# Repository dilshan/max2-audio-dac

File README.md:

# 24-bit Stereo Audio DAC for Raspberry Pi

This is a 24-bit stereo DAC, which is specifically built for Raspberry Pi boards. This R-2R ladder DAC is developing around Intel / Altera *EPM240T100C5N* CPLD.

DAC which described in this repo can directly connect with the I2S interface of Raspberry Pi boards. The recommended supply voltage for this DAC is 5V to 8V.

The *MCP602* opamp of this module is capable to drive headphone directly. An external AF power amplifier must pair with this module to obtain a higher output power.

This repository contains all the files and binaries to build DAC, which including *Intel Quartus* Project files, Raspberry Pi Device Tree Overlays, etc.

This is certified open-source hardware project. All the content of this project are distributed under the terms of the following license:

-   Hardware License: [CC BY 4.0](https://creativecommons.org/licenses/by/4.0/)
-   Software License: [MIT](https://github.com/dilshan/max2-audio-dac/blob/master/LICENSE)
-   [Documentation](https://github.com/dilshan/max2-audio-dac/wiki) License: [CC BY 4.0](https://creativecommons.org/licenses/by/4.0/)

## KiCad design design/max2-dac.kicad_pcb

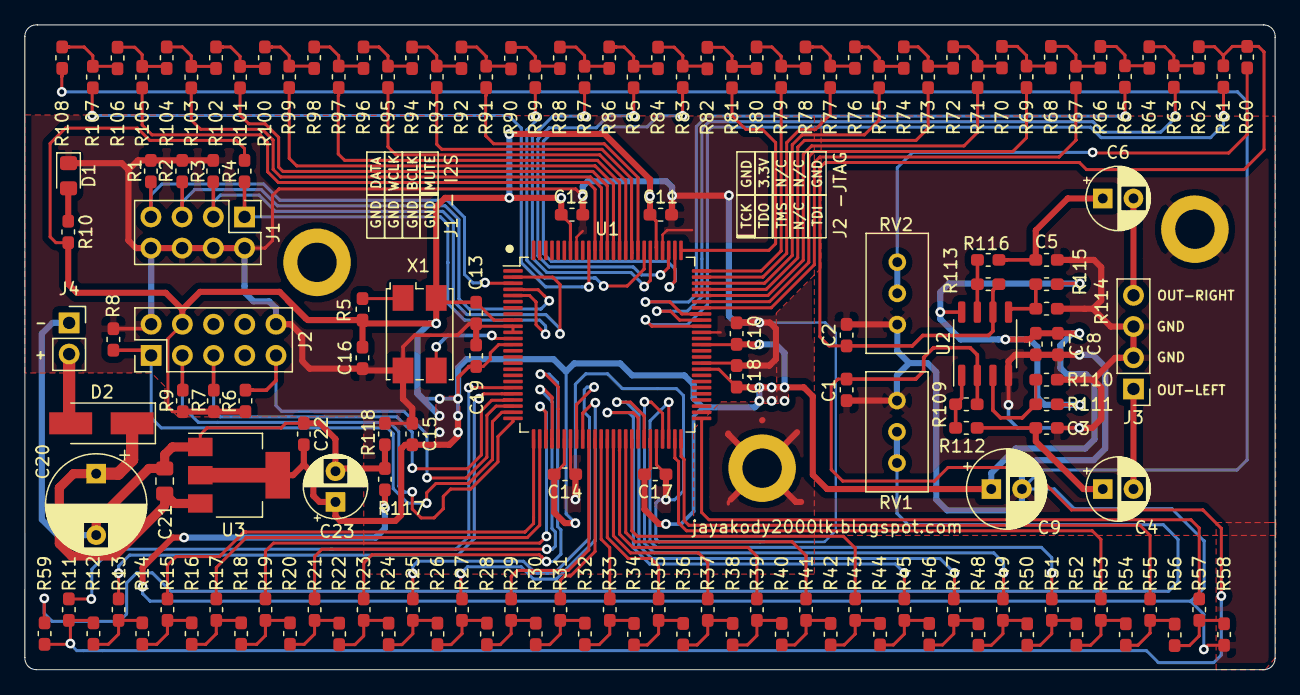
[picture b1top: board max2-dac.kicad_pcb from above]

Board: 2 copper layers, 101.8 x 52.5 mm, 156 parts (0 on the bottom side), 123 nets.

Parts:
 : MountingHole_3.2mm_M3_ISO14580_Pad
 #2,  #3: MountingHole_3.2mm_M3_ISO14580_Pad
C1, C2: 100pF; C_0603_1608Metric_Pad1.05x0.95mm_HandSolder
C3, C5, C8: 0.01MFD; C_0603_1608Metric_Pad1.05x0.95mm_HandSolder
C4, C6: 4.7MFD; CP_Radial_D5.0mm_P2.50mm
C7, C10, C11, C12, C13, C14, C15, C16, C17, C18, C19: 0.1MFD; C_0603_1608Metric_Pad1.05x0.95mm_HandSolder
C9: 100MFD; CP_Radial_D6.3mm_P2.50mm
C20: 470MFD; CP_Radial_D8.0mm_P5.00mm
C21: 0.1MFD; C_0805_2012Metric_Pad1.15x1.40mm_HandSolder
C22: 0.22MFD; C_0603_1608Metric_Pad1.05x0.95mm_HandSolder
C23: 10MFD; CP_Radial_D5.0mm_P2.50mm
D1: PWR; LED_0805_2012Metric_Pad1.15x1.40mm_HandSolder
D2: SS14; D_SMA_Handsoldering
J1: I2S; PinHeader_2x04_P2.54mm_Vertical
J2: JTAG; PinHeader_2x05_P2.54mm_Vertical
J3: AF-OUT; PinHeader_1x04_P2.54mm_Vertical
J4: DC-IN; PinSocket_1x02_P2.54mm_Vertical
R1, R2, R3, R4: 22K; R_0603_1608Metric_Pad1.05x0.95mm_HandSolder
R5, R117, R118: 0R; R_0603_1608Metric_Pad1.05x0.95mm_HandSolder
R6, R7, R8, R9: 10K; R_0603_1608Metric_Pad1.05x0.95mm_HandSolder
R10: 1K; R_0603_1608Metric_Pad1.05x0.95mm_HandSolder
R11, R13, R15, R17, R19, R21, R23, R25, R27, R29, R31, R33, R35, R37, R39, R41, R43, R45, R47, R49, R51, R53, R55, R57, R58, R61, R63, R65, R67, R69, R71, R73, R75, R77, R79, R81, R83, R85, R87, R89, R91, R93, R95, R97, R99, R101, R103, R105, R107, R108: 15K; R_0603_1608Metric_Pad1.05x0.95mm_HandSolder
R12, R14, R16, R18, R20, R22, R24, R26, R28, R30, R32, R34, R36, R38, R40, R42, R44, R46, R48, R50, R52, R54, R56, R59, R60, R62, R64, R66, R68, R70, R72, R74, R76, R78, R80, R82, R84, R86, R88, R90, R92, R94, R96, R98, R100, R102, R104, R106: 7.5K; R_0603_1608Metric_Pad1.05x0.95mm_HandSolder
R109, R113: 2.2K; R_0603_1608Metric_Pad1.05x0.95mm_HandSolder
R110, R111, R114, R115: 100K; R_0603_1608Metric_Pad1.05x0.95mm_HandSolder
R112, R116: 560R; R_0603_1608Metric_Pad1.05x0.95mm_HandSolder
RV1, RV2: 10K; Potentiometer_Bourns_3296W_Vertical
U1: EPM240T100C5; LQFP-100_14x14mm_P0.5mm
U2: MCP602; SO-8_3.9x4.9mm_P1.27mm
U3: LM1117-3.3; SOT-223-3_TabPin2
X1: 50.00MHz; Crystal_SMD_7050-4Pin_7.0x5.0mm

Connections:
+3V3: C7.2, C8.2, C9.1, C10.2, C11.2, C12.2, C13.2, C14.2, C15.2, C16.2, C17.2, C18.2, C19.2, C22.2, C23.1, J2.4, R4.1, R5.2, R6.2, R7.1, R9.2, R10.2, R111.2, R115.2, U1.9, U1.13, U1.31, U1.45, U1.59, U1.63, U1.80, U1.94, U2.8, U3.2, X1.4
BCLK: J1.3, R3.1, U1.2
CLK: U1.12, X1.3
DIN: J1.7, R1.1, U1.3
GND: C20.2, C21.1, C22.1, C23.2, J4.1, R117.2, R118.2, U3.1
GNDA: #2.1, #3.1, C1.2, C2.2, C3.1, C5.1, C7.1, C8.1, C9.2, J3.2, J3.3, R58.2, R108.2, R110.1, R114.1, R117.1, RV1.1, RV2.1, U2.4
GNDD: C10.1, C11.1, C12.1, C13.1, C14.1, C15.1, C16.1, C17.1, C18.1, C19.1, D1.1, J1.2, J1.4, J1.6, J1.8, J2.2, J2.10, R1.2, R2.2, R3.2, R8.1, R118.1, U1.10, U1.11, U1.32, U1.46, U1.60, U1.65, U1.79, U1.93, X1.2
LEFT0: R57.1, U1.51
LEFT1: R55.1, U1.50
LEFT2: R53.1, U1.49
LEFT3: R51.1, U1.48
LEFT4: R49.1, U1.47
LEFT5: R47.1, U1.44
LEFT6: R45.1, U1.43
LEFT7: R43.1, U1.42
LEFT8: R41.1, U1.41
LEFT9: R39.1, U1.40
LEFT10: R37.1, U1.39
LEFT11: R35.1, U1.38
LEFT12: R33.1, U1.37
LEFT13: R31.1, U1.36
LEFT14: R29.1, U1.35
LEFT15: R27.1, U1.34
LEFT16: R25.1, U1.33
LEFT17: R23.1, U1.30
LEFT18: R21.1, U1.29
LEFT19: R19.1, U1.28
LEFT20: R17.1, U1.27
LEFT21: R15.1, U1.26
LEFT22: R13.1, U1.21
LEFT23: R11.1, U1.20
LEFT-DAC: C1.1, R11.2, R12.1, R59.2, R109.2, U2.2
LEFT-OUT: C4.2, J3.1
MUTE: J1.1, R4.2, U1.5
unnamed: C3.2, C4.1, R112.1
unnamed: C5.2, C6.1, R116.1
unnamed: D1.2, R10.1
unnamed: D2.2, J4.2
unnamed: R5.1, X1.1
unnamed: R12.2, R13.2, R14.1
unnamed: R14.2, R15.2, R16.1
unnamed: R16.2, R17.2, R18.1
unnamed: R18.2, R19.2, R20.1
unnamed: R20.2, R21.2, R22.1
unnamed: R22.2, R23.2, R24.1
unnamed: R24.2, R25.2, R26.1
unnamed: R26.2, R27.2, R28.1
unnamed: R28.2, R29.2, R30.1
unnamed: R30.2, R31.2, R32.1
unnamed: R32.2, R33.2, R34.1
unnamed: R34.2, R35.2, R36.2
unnamed: R36.1, R37.2, R38.2
unnamed: R38.1, R39.2, R40.2
unnamed: R40.1, R41.2, R42.2
unnamed: R42.1, R43.2, R44.2
unnamed: R44.1, R45.2, R46.2
unnamed: R46.1, R47.2, R48.2
unnamed: R48.1, R49.2, R50.2
unnamed: R50.1, R51.2, R52.2
unnamed: R52.1, R53.2, R54.2
unnamed: R54.1, R55.2, R56.2
unnamed: R56.1, R57.2, R58.1
unnamed: R59.1, RV1.2, RV1.3
unnamed: R60.1, RV2.2, RV2.3
unnamed: R62.2, R63.2, R64.1
unnamed: R64.2, R65.2, R66.1
unnamed: R66.2, R67.2, R68.1
unnamed: R68.2, R69.2, R70.1
unnamed: R70.2, R71.2, R72.1
unnamed: R72.2, R73.2, R74.1
unnamed: R74.2, R75.2, R76.1
unnamed: R76.2, R77.2, R78.1
unnamed: R78.2, R79.2, R80.1
unnamed: R80.2, R81.2, R82.1
unnamed: R82.2, R83.2, R84.1
unnamed: R84.2, R85.2, R86.2
unnamed: R86.1, R87.2, R88.2
unnamed: R88.1, R89.2, R90.2
unnamed: R90.1, R91.2, R92.2
unnamed: R92.1, R93.2, R94.2
unnamed: R94.1, R95.2, R96.2
unnamed: R96.1, R97.2, R98.2
unnamed: R100.1, R101.2, R102.2
unnamed: R98.1, R99.2, R100.2
unnamed: R102.1, R103.2, R104.2
unnamed: R104.1, R105.2, R106.2
unnamed: R106.1, R107.2, R108.1
unnamed: R109.1, R112.2, U2.1
unnamed: R110.2, R111.1, U2.3
unnamed: R113.1, R116.2, U2.7
unnamed: R114.2, R115.1, U2.5
RIGHT0: R107.1, U1.91
RIGHT1: R105.1, U1.90
RIGHT2: R103.1, U1.89
RIGHT3: R101.1, U1.88
RIGHT4: R99.1, U1.87
RIGHT5: R97.1, U1.86
RIGHT6: R95.1, U1.85
RIGHT7: R93.1, U1.84
RIGHT8: R91.1, U1.83
RIGHT9: R89.1, U1.82
RIGHT10: R87.1, U1.81
RIGHT11: R85.1, U1.78
RIGHT12: R83.1, U1.77
RIGHT13: R81.1, U1.76
RIGHT14: R79.1, U1.75
RIGHT15: R77.1, U1.74
RIGHT16: R75.1, U1.73
RIGHT17: R73.1, U1.72
RIGHT18: R71.1, U1.71
RIGHT19: R69.1, U1.70
RIGHT20: R67.1, U1.69
RIGHT21: R65.1, U1.68
RIGHT22: R63.1, U1.67
RIGHT23: R61.1, U1.66
RIGHT-DAC: C2.1, R60.2, R61.2, R62.1, R113.2, U2.6
RIGHT-OUT: C6.2, J3.4
TCK: J2.1, R8.2, U1.24
TDI: J2.9, R6.1, U1.23
TDO: J2.3, R9.1, U1.25
TMS: J2.5, R7.2, U1.22
VCC: C20.1, C21.2, D2.1, U3.3
WCLK: J1.5, R2.1, U1.4

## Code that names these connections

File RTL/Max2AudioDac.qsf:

# -------------------------------------------------------------------------- #
#
# Copyright (C) 2018  Intel Corporation. All rights reserved.
# Your use of Intel Corporation's design tools, logic functions 
# and other software and tools, and its AMPP partner logic 
# functions, and any output files from any of the foregoing 
# (including device programming or simulation files), and any 
# associated documentation or information are expressly subject 
# to the terms and conditions of the Intel Program License 
# Subscription Agreement, the Intel Quartus Prime License Agreement,
# the Intel FPGA IP License Agreement, or other applicable license
# agreement, including, without limitation, that your use is for
# the sole purpose of programming logic devices manufactured by
# Intel and sold by Intel or its authorized distributors.  Please
# refer to the applicable agreement for further details.
#
# -------------------------------------------------------------------------- #
#
# Quartus Prime
# Version 18.1.0 Build 625 09/12/2018 SJ Lite Edition
# Date created = 13:50:59  August 08, 2019
#
# -------------------------------------------------------------------------- #
#
# Notes:
#
# 1) The default values for assignments are stored in the file:
#		Max2AudioDac_assignment_defaults.qdf
#    If this file doesn't exist, see file:
#		assignment_defaults.qdf
#
# 2) Altera recommends that you do not modify this file. This
#    file is updated automatically by the Quartus Prime software
#    and any changes you make may be lost or overwritten.
#
# -------------------------------------------------------------------------- #


set_global_assignment -name FAMILY "MAX II"
set_global_assignment -name DEVICE EPM240T100C5
set_global_assignment -name TOP_LEVEL_ENTITY Max2AudioDac
set_global_assignment -name ORIGINAL_QUARTUS_VERSION 18.1.0
set_global_assignment -name PROJECT_CREATION_TIME_DATE "13:50:59  AUGUST 08, 2019"
set_global_assignment -name LAST_QUARTUS_VERSION "18.1.0 Lite Edition"
set_global_assignment -name PROJECT_OUTPUT_DIRECTORY output_files
set_global_assignment -name MIN_CORE_JUNCTION_TEMP 0
set_global_assignment -name MAX_CORE_JUNCTION_TEMP 85
set_global_assignment -name ERROR_CHECK_FREQUENCY_DIVISOR "-1"
set_global_assignment -name POWER_EXT_SUPPLY_VOLTAGE_TO_REGULATOR 3.3V
set_global_assignment -name EDA_SIMULATION_TOOL "ModelSim-Altera (Verilog)"
set_global_assignment -name EDA_TIME_SCALE "1 ps" -section_id eda_simulation
set_global_assignment -name EDA_OUTPUT_DATA_FORMAT "VERILOG HDL" -section_id eda_simulation
set_global_assignment -name VERILOG_FILE Max2AudioDac.v
set_global_assignment -name POWER_PRESET_COOLING_SOLUTION "NO HEAT SINK WITH STILL AIR"
set_global_assignment -name VECTOR_WAVEFORM_FILE waveform.vwf
set_location_assignment PIN_51 -to lout[0]
set_location_assignment PIN_2 -to bclk
set_location_assignment PIN_3 -to din
set_location_assignment PIN_34 -to lout[15]
set_instance_assignment -name IO_STANDARD "3.3-V LVCMOS" -to lout[14]
set_instance_assignment -name IO_STANDARD "3.3-V LVCMOS" -to lout[15]
set_instance_assignment -name IO_STANDARD "3.3-V LVCMOS" -to din
set_instance_assignment -name IO_STANDARD "3.3-V LVCMOS" -to bclk
set_instance_assignment -name IO_STANDARD "3.3-V LVCMOS" -to wclk
set_instance_assignment -name IO_STANDARD "3.3-V LVCMOS" -to rout[1]
set_instance_assignment -name IO_STANDARD "3.3-V LVCMOS" -to lout[13]
set_instance_assignment -name IO_STANDARD "3.3-V LVCMOS" -to lout[12]
set_instance_assignment -name IO_STANDARD "3.3-V LVCMOS" -to lout[11]
set_instance_assignment -name IO_STANDARD "3.3-V LVCMOS" -to lout[10]
set_instance_assignment -name IO_STANDARD "3.3-V LVCMOS" -to lout[9]
set_location_assignment PIN_35 -to lout[14]
set_location_assignment PIN_36 -to lout[13]
set_location_assignment PIN_37 -to lout[12]
set_location_assignment PIN_38 -to lout[11]
set_location_assignment PIN_39 -to lout[10]
set_location_assignment PIN_40 -to lout[9]
set_location_assignment PIN_41 -to lout[8]
set_location_assignment PIN_42 -to lout[7]
set_location_assignment PIN_43 -to lout[6]
set_location_assignment PIN_44 -to lout[5]
set_location_assignment PIN_47 -to lout[4]
set_location_assignment PIN_48 -to lout[3]
set_location_assignment PIN_49 -to lout[2]
set_location_assignment PIN_50 -to lout[1]
set_location_assignment PIN_74 -to rout[15]
set_location_assignment PIN_75 -to rout[14]
set_location_assignment PIN_76 -to rout[13]
set_location_assignment PIN_77 -to rout[12]
set_location_assignment PIN_78 -to rout[11]
set_location_assignment PIN_81 -to rout[10]
set_location_assignment PIN_82 -to rout[9]
set_location_assignment PIN_84 -to rout[7]
set_location_assignment PIN_83 -to rout[8]
set_location_assignment PIN_86 -to rout[5]
set_location_assignment PIN_85 -to rout[6]
set_location_assignment PIN_87 -to rout[4]
set_location_assignment PIN_88 -to rout[3]
set_location_assignment PIN_89 -to rout[2]
set_location_assignment PIN_90 -to rout[1]
set_location_assignment PIN_91 -to rout[0]
set_location_assignment PIN_4 -to wclk
set_location_assignment PIN_33 -to lout[16]
set_location_assignment PIN_30 -to lout[17]
set_location_assignment PIN_29 -to lout[18]
set_location_assignment PIN_28 -to lout[19]
set_location_assignment PIN_27 -to lout[20]
set_location_assignment PIN_26 -to lout[21]
set_location_assignment PIN_21 -to lout[22]
set_location_assignment PIN_20 -to lout[23]
set_location_assignment PIN_73 -to rout[16]
set_location_assignment PIN_72 -to rout[17]
set_location_assignment PIN_71 -to rout[18]
set_location_assignment PIN_70 -to rout[19]
set_location_assignment PIN_69 -to rout[20]
set_location_assignment PIN_68 -to rout[21]
set_location_assignment PIN_67 -to rout[22]
set_location_assignment PIN_66 -to rout[23]
set_instance_assignment -name IO_STANDARD "3.3-V LVCMOS" -to lout[23]
set_instance_assignment -name IO_STANDARD "3.3-V LVCMOS" -to lout[22]
set_instance_assignment -name IO_STANDARD "3.3-V LVCMOS" -to lout[21]
set_instance_assignment -name IO_STANDARD "3.3-V LVCMOS" -to lout[20]
set_instance_assignment -name IO_STANDARD "3.3-V LVCMOS" -to lout[19]
set_instance_assignment -name IO_STANDARD "3.3-V LVCMOS" -to lout[18]
set_instance_assignment -name IO_STANDARD "3.3-V LVCMOS" -to lout[17]
set_instance_assignment -name IO_STANDARD "3.3-V LVCMOS" -to lout[16]
set_instance_assignment -name IO_STANDARD "3.3-V LVCMOS" -to lout[8]
set_instance_assignment -name IO_STANDARD "3.3-V LVCMOS" -to lout[7]
set_instance_assignment -name IO_STANDARD "3.3-V LVCMOS" -to lout[6]
set_instance_assignment -name IO_STANDARD "3.3-V LVCMOS" -to lout[5]
set_instance_assignment -name IO_STANDARD "3.3-V LVCMOS" -to lout[4]
set_instance_assignment -name IO_STANDARD "3.3-V LVCMOS" -to lout[3]
set_instance_assignment -name IO_STANDARD "3.3-V LVCMOS" -to lout[2]
set_instance_assignment -name IO_STANDARD "3.3-V LVCMOS" -to lout[1]
set_instance_assignment -name IO_STANDARD "3.3-V LVCMOS" -to lout[0]
set_instance_assignment -name IO_STANDARD "3.3-V LVCMOS" -to lout
set_instance_assignment -name IO_STANDARD "3.3-V LVCMOS" -to rout[23]
set_instance_assignment -name IO_STANDARD "3.3-V LVCMOS" -to rout[0]
set_instance_assignment -name IO_STANDARD "3.3-V LVCMOS" -to rout[2]
set_instance_assignment -name IO_STANDARD "3.3-V LVCMOS" -to rout[3]
set_instance_assignment -name IO_STANDARD "3.3-V LVCMOS" -to rout[4]
set_instance_assignment -name IO_STANDARD "3.3-V LVCMOS" -to rout[5]
set_instance_assignment -name IO_STANDARD "3.3-V LVCMOS" -to rout[6]
set_instance_assignment -name IO_STANDARD "3.3-V LVCMOS" -to rout[7]
set_instance_assignment -name IO_STANDARD "3.3-V LVCMOS" -to rout[8]
set_instance_assignment -name IO_STANDARD "3.3-V LVCMOS" -to rout[9]
set_instance_assignment -name IO_STANDARD "3.3-V LVCMOS" -to rout[10]
set_instance_assignment -name IO_STANDARD "3.3-V LVCMOS" -to rout[11]
set_instance_assignment -name IO_STANDARD "3.3-V LVCMOS" -to rout[13]
set_instance_assignment -name IO_STANDARD "3.3-V LVCMOS" -to rout[14]
set_instance_assignment -name IO_STANDARD "3.3-V LVCMOS" -to rout[15]
set_instance_assignment -name IO_STANDARD "3.3-V LVCMOS" -to rout[16]
set_instance_assignment -name IO_STANDARD "3.3-V LVCMOS" -to rout[17]
set_instance_assignment -name IO_STANDARD "3.3-V LVCMOS" -to rout[18]
set_instance_assignment -name IO_STANDARD "3.3-V LVCMOS" -to rout[19]
set_instance_assignment -name IO_STANDARD "3.3-V LVCMOS" -to rout[20]
set_instance_assignment -name IO_STANDARD "3.3-V LVCMOS" -to rout[22]
set_instance_assignment -name IO_STANDARD "3.3-V LVCMOS" -to rout[21]
set_instance_assignment -name IO_STANDARD "3.3-V LVCMOS" -to rout[12]
set_instance_assignment -name IO_STANDARD "3.3-V LVCMOS" -to rout
set_location_assignment PIN_12 -to clk
set_instance_assignment -name IO_STANDARD "3.3-V LVCMOS" -to clk
set_location_assignment PIN_5 -to mute
set_instance_assignment -name IO_STANDARD "3.3-V LVCMOS" -to mute

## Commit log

2020-01-12 Initial version of MAX2-DAC design files.
2020-01-12 Add image into documentation.
2020-01-15 Add software license document.
2020-01-15 Update readme file with software license.
2020-01-15 Add link to project documentation wiki.
2020-01-15 Update documentation with shield icons.
2020-01-27 Include OSHW certificate logo into repo.
2020-01-27 Add OSHW certification information.
2020-01-27 Add link to certification.oshwa.org.

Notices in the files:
design/max2-dac.kicad_pcb:
This work is licensed under a Creative Commons
Attribution 4.0 International License.
